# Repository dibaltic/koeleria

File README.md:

# Koeleria

## Features
- 30 keys with splay and column stagger
- nice!view and nice!nano
- Hotswap sockets, no direct solder option for switches
- Low profile Choc V1 switches with Choc spacing
- Exclusively wireless using [ZMK firmware](https://zmk.dev/)
- Cases are designed to be low profile with recessed adhesive feet
- A variety of cases can be found in the [3d_Print](https://github.com/dibaltic/koeleria/tree/main/3d_Print) folder. Including enclosed split, minimal split, unibody, storage case, and variety of tenting angles.

### Design

- My first ergo keyboard was an MX Sweep, and then shortly after a wireless Choc Sweep. I wanted my thumbs less tucked, to use my pinky less, and reach less with my index finger. I also wanted to have the option for a display. 

- My goal was to make keyboard to be as low profile as I could. The case adds 1mm in height to the PCB. There is a total of 1.5mm added height with the specified silicone feet installed on the case.

- In the majority of the photos I am using [KLP Lamé](https://github.com/braindefender/KLP-Lame-Keycaps) keycaps with LSDA profile thumbs, but the case was designed around clearing normal keycaps as you can see in the photos of the unibody case with a full set LSDA keycaps installed.

- All the files for the keyboard and cases have been shared if you would like to modify anything to better suit your needs.

# B.O.M 

#### Required

- 1x PCB pair (production files can be found [here](https://github.com/dibaltic/koeleria/tree/main/PCB/Gerbers))
- 30x Kailh Choc V1 switches
- 30x Key caps
- 30x Kailh Choc hotswap sockets (no direct switch soldering support)
- 30x SMD diodes 1n4148w (SOD-123)
- 2x nice!nano
- 2x batteries (301230)
- 2x female headers (mcu sockets)
- 48x header pins (mill-max or other solution)

#### Optional

- 2× nice!view
- 2× Reset switch (B3U-1000P(M))
- 2× Power switch (MSK 12C02)
- 10× adhesive silicone feet 8mmx2.5mm
> Note: If you are using a case from [3d_Print folder](https://github.com/dibaltic/koeleria/tree/main/3d_Print) you will need M2 hardware, heatserts, and additional non-slip feet. More information can be found in the corresponding readme.

# Firmware

- [zmk_koeleria](https://github.com/dibaltic/zmk_koeleria)

# Pictures

# Inspirations and Credit
I took inspiration from the [Urchin](https://github.com/duckyb/urchin), [Sweep](https://github.com/davidphilipbarr/Sweep), and [Luna](https://github.com/mindhatch/keyboards). I used footprints from the Urchin, and used [ergogen](https://ergogen.ceoloide.com/) to get the physical key placement configured before designing the rest in Kicad and Freecad.

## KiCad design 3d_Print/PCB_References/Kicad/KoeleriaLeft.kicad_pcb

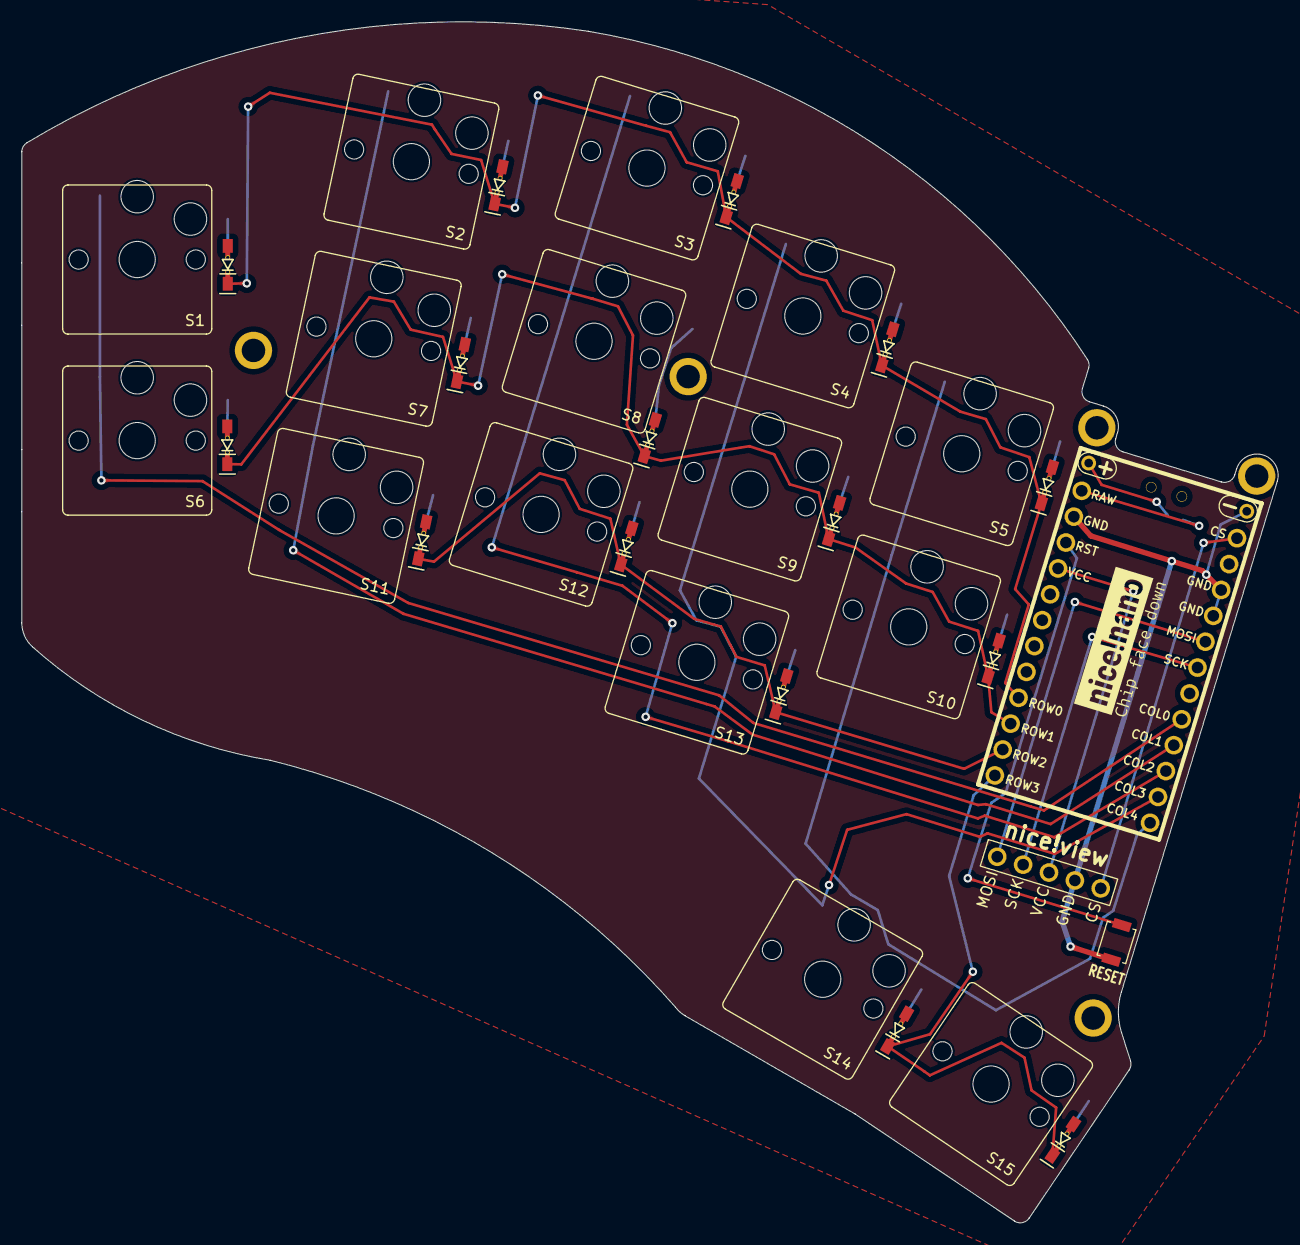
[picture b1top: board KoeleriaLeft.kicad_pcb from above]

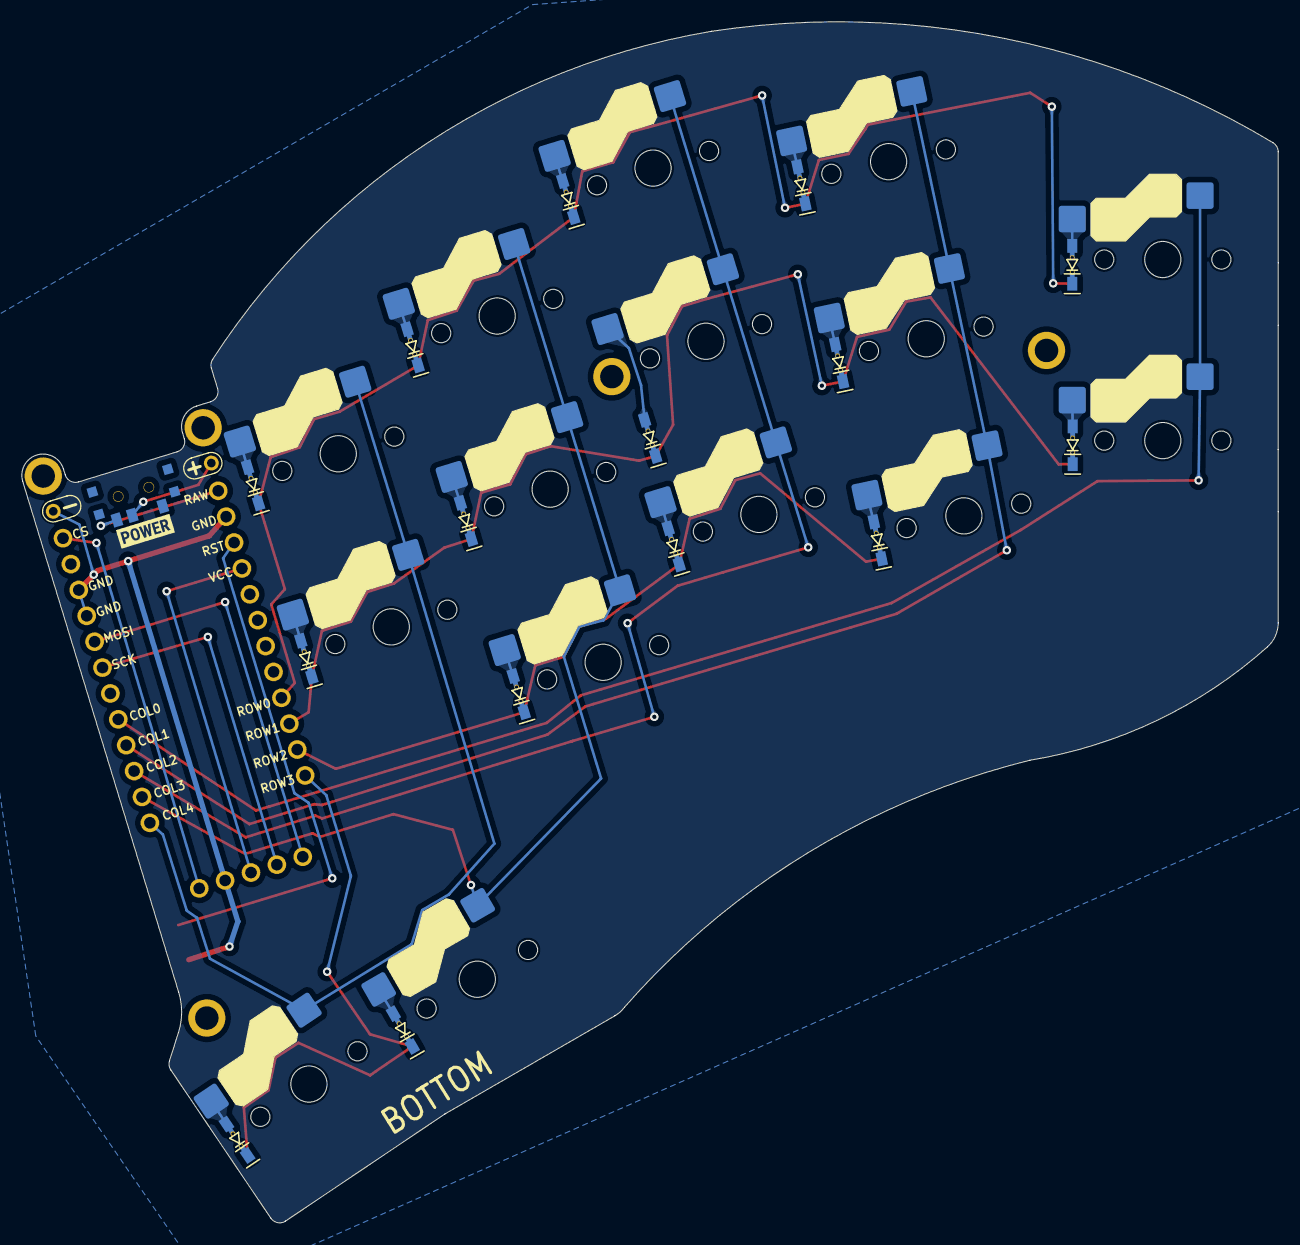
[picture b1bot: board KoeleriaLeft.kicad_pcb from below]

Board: 2 copper layers, 118.0 x 112.8 mm, 39 parts (18 on the bottom side), 15 nets.

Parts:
Bat+0, Bat+0#2: MountingHole_Pad; ducky_1pin_Battery
D1, D2, D3, D5, D6, D7, D8, D9, D10, D11, D12, D13, D14, D15: ducky_diode
D4: duckey diode
DISP1: ducky_nice_view
RESET: SW_SPST_B3U-1000P
S1, S2, S3, S4, S5, S6, S7, S8, S9, S10, S11, S12, S13, S14, S15: ducky_Hotswap_Kailh_Choc_V1_tweaked
SW_POWER1: SW_SPDT; smt-slider-switch
U2: nice_nano; ducky_nice_nano
kibuzzard-636588C8: G***; kibuzzard-636588C8
kibuzzard-6365884B: G***; kibuzzard-6365884B
kibuzzard-6365951E: G***; kibuzzard-6365951E

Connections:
index_bottom: D9.2, S6.2
index_home: D10.2, S11.2
index_top: D11.2, S12.2
inner_bottom: D12.2, S13.2
inner_home: D13.2, S10.2
inner_thumb: D14.2, S14.2
middle_bottom: D6.2, S8.2
middle_home: D7.2, S9.2
middle_top: D8.2, S5.2
pinky_home: D1.2, S2.2
pinky_top: D2.2, S3.2
ring_bottom: D3.2, S4.2
ring_home: D4.2, S1.2
ring_top: D5.2, S7.2
space_thumb: D15.2, S15.2

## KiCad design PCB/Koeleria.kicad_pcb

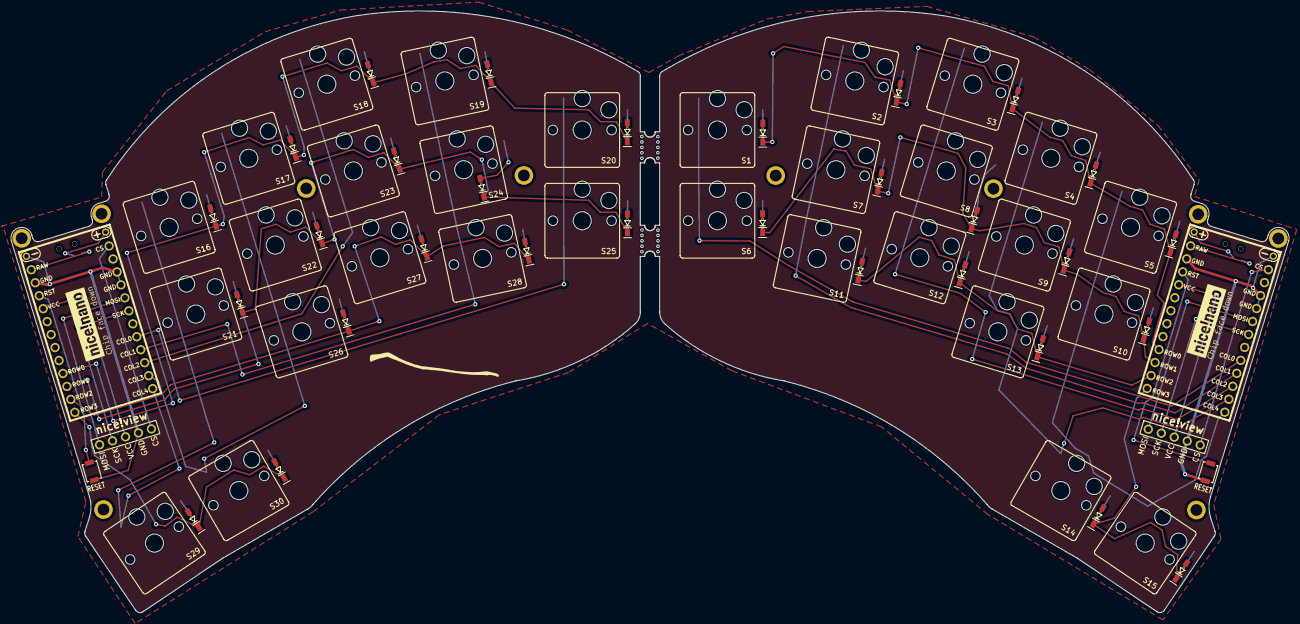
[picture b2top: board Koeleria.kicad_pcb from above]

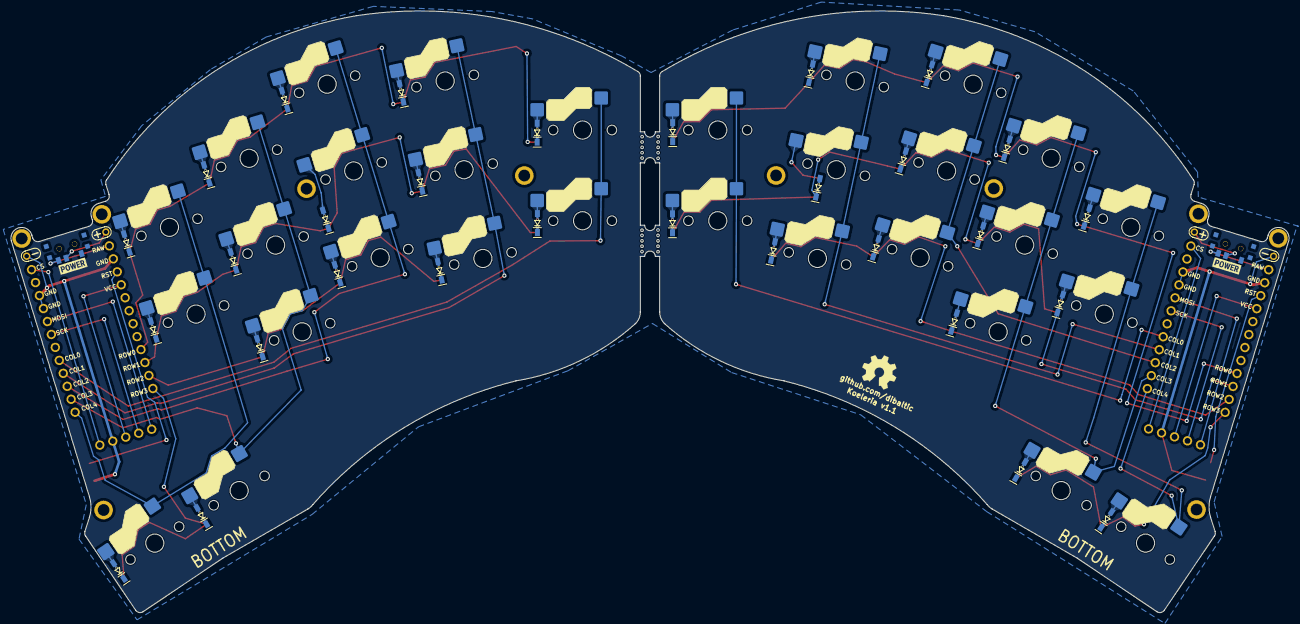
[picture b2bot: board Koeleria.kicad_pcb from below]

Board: 2 copper layers, 239.5 x 112.8 mm, 80 parts (36 on the bottom side), 30 nets.

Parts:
Bat+0, Bat+0#2, Bat+0#3, Bat+0#4: MountingHole_Pad; ducky_1pin_Battery
D1, D2, D3, D5, D6, D7, D8, D9, D10, D11, D12, D13, D14, D15, D16, D17, D19, D20, D21, D22, D23, D24, D25, D26, D27, D28, D29, D30: ducky_diode
D4, D18: duckey diode
DISP1, DISP1#2: ducky_nice_view
RESET: SW_SPST_B3U-1000P
RESET#2: SW_SPST_B3U-1000P
S1, S2, S3, S4, S5, S6, S7, S8, S9, S10, S11, S12, S13, S14, S15, S16, S17, S18, S19, S20, S21, S22, S23, S24, S25, S26, S27, S28, S29, S30: ducky_Hotswap_Kailh_Choc_V1_tweaked
SW_POWER1, SW_POWER1#2: SW_SPDT; smt-slider-switch
U2, U2#2: nice_nano; ducky_nice_nano
kibuzzard-636588C8, kibuzzard-636588C8#2: G***; kibuzzard-636588C8
kibuzzard-6365884B, kibuzzard-6365884B#2: G***; kibuzzard-6365884B
kibuzzard-6365951E, kibuzzard-6365951E#2: G***; kibuzzard-6365951E
mouse-bite-2mm-slot, mouse-bite-2mm-slot#2: VAL**; mouse-bite-5mm-slot-with-space-for-track

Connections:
index_bottom: D9.2, S6.2
index_home: D10.2, S11.2
index_top: D11.2, S12.2
inner_bottom: D12.2, S13.2
inner_home: D13.2, S10.2
inner_thumb: D14.2, S14.2
middle_bottom: D6.2, S8.2
middle_home: D7.2, S9.2
middle_top: D8.2, S5.2
mirror_index_bottom: D24.2, S25.2
mirror_index_home: D25.2, S28.2
mirror_index_top: D26.2, S27.2
mirror_inner_bottom: D27.2, S26.2
mirror_inner_home: D28.2, S21.2
mirror_inner_thumb: D29.2, S30.2
mirror_middle_bottom: D21.2, S23.2
mirror_middle_home: D22.2, S22.2
mirror_middle_top: D23.2, S16.2
mirror_pinky_home: D16.2, S19.2
mirror_pinky_top: D17.2, S18.2
mirror_ring_bottom: D18.2, S17.2
mirror_ring_home: D19.2, S20.2
mirror_ring_top: D20.2, S24.2
mirror_space_thumb: D30.2, S29.2
pinky_home: D1.2, S2.2
pinky_top: D2.2, S3.2
ring_bottom: D3.2, S4.2
ring_home: D4.2, S1.2
ring_top: D5.2, S7.2
space_thumb: D15.2, S15.2

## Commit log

2025-07-12 Rename README.md.txt to README.md
2025-07-12 Rename JLPCB_settings.md.txt to JLPCB_settings.md
2025-07-12 Rename koeleria.yaml.txt to koeleria.yaml
